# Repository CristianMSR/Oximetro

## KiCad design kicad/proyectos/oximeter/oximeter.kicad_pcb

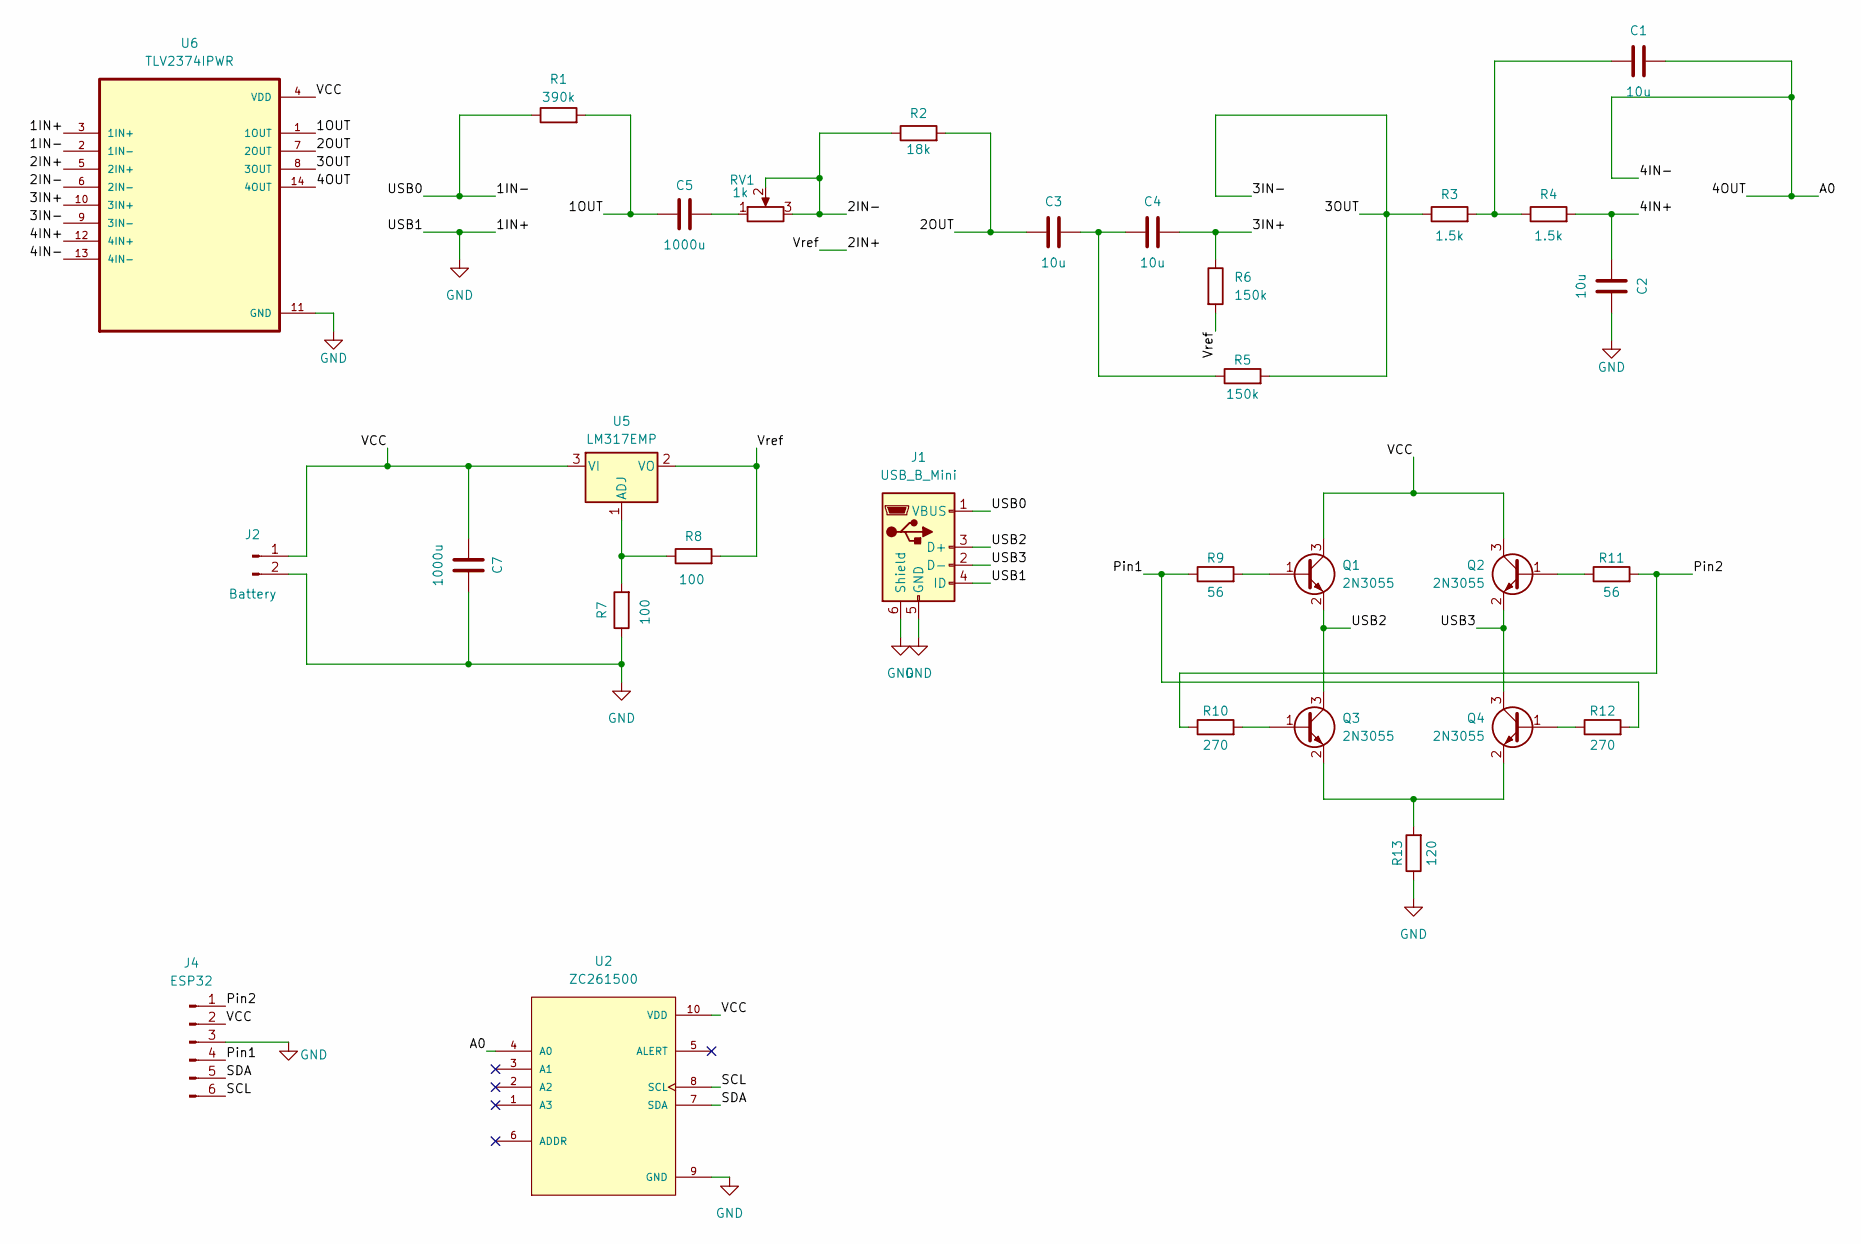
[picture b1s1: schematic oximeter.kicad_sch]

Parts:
C1, C2, C3, C4: 10u; CP_Elec_4x3
C5, C7: 1000u; CP_Radial_D8.0mm_P3.80mm
J1: USB_B_Mini; miniUSB-B-20
J2: Battery; PinHeader_1x02_P2.00mm_Vertical
J4: ESP32; PinHeader_1x06_P2.54mm_Vertical
Q1, Q2, Q3, Q4: 2N3055; BJT-NPN-SMD
R1: 390k; R_1206_3216Metric_Pad1.30x1.75mm_HandSolder
R2: 18k; R_1206_3216Metric_Pad1.30x1.75mm_HandSolder
R3, R4: 1.5k; R_1206_3216Metric_Pad1.30x1.75mm_HandSolder
R5, R6: 150k; R_1206_3216Metric_Pad1.30x1.75mm_HandSolder
R7, R8: 100; R_1206_3216Metric_Pad1.30x1.75mm_HandSolder
R9, R11: 56; R_1206_3216Metric_Pad1.30x1.75mm_HandSolder
R10, R12: 270; R_1206_3216Metric_Pad1.30x1.75mm_HandSolder
R13: 120; R_1206_3216Metric_Pad1.30x1.75mm_HandSolder
RV1: 1k; TRIM_3296W-1-103
U2: ZC261500; MODULE_ZC261500; PARTREV NA
U5: LM317EMP; SOT-223-3_TabPin2
U6: TLV2374IPWR; opamp-TLV2374IPWR

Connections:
/1IN-: J1.1 (VBUS), R1.1, U6.2 (1IN-)
/1OUT: C5.1, R1.2, U6.1 (1OUT)
/2IN+: R6.2, R8.2, U5.2 (VO), U6.5 (2IN+)
/2IN-: R2.1, RV1.2, RV1.3, U6.6 (2IN-)
/2OUT: C3.1, R2.2, U6.7 (2OUT)
/3IN+: C4.2, R6.1, U6.10 (3IN+)
/3IN-: R3.1, R5.2, U6.8 (3OUT), U6.9 (3IN-)
/4IN+: C2.1, R4.2, U6.12 (4IN+)
/4IN-: C1.2, U2.4 (A0), U6.13 (4IN-), U6.14 (4OUT)
/Pin1: J4.4, R9.1, R12.2
/Pin2: J4.1, R10.1, R11.2
/SCL: J4.6, U2.8 (SCL)
/SDA: J4.5, U2.7 (SDA)
/USB2: J1.3 (D+), Q1.2 (E), Q3.3 (C)
/USB3: J1.2 (D-), Q2.2 (E), Q4.3 (C)
/VCC: C7.1, J2.1, J4.2, Q1.3 (C), Q2.3 (C), U2.10 (VDD), U5.3 (VI), U6.4 (VDD)
GND: C2.2, C7.2, J1.4 (ID), J1.5 (GND), J1.6 (Shield), J2.2, J4.3, R7.1, R13.1, U2.9 (GND), U6.3 (1IN+), U6.11 (GND)
unnamed: C1.1, R3.2, R4.1
unnamed: C3.2, C4.1, R5.1
unnamed: C5.2, RV1.1
unnamed: Q1.1 (B), R9.2
unnamed: Q2.1 (B), R11.1
unnamed: Q3.1 (B), R10.2
unnamed: Q3.2 (E), Q4.2 (E), R13.2
unnamed: Q4.1 (B), R12.1
unnamed: R7.2, R8.1, U5.1 (ADJ)

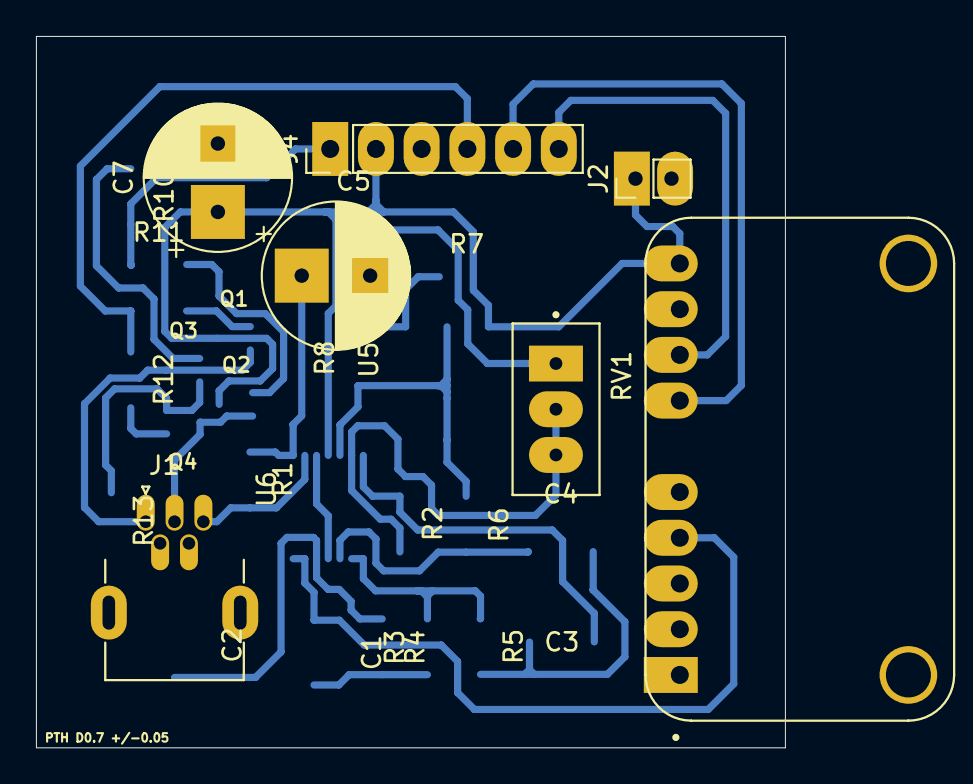
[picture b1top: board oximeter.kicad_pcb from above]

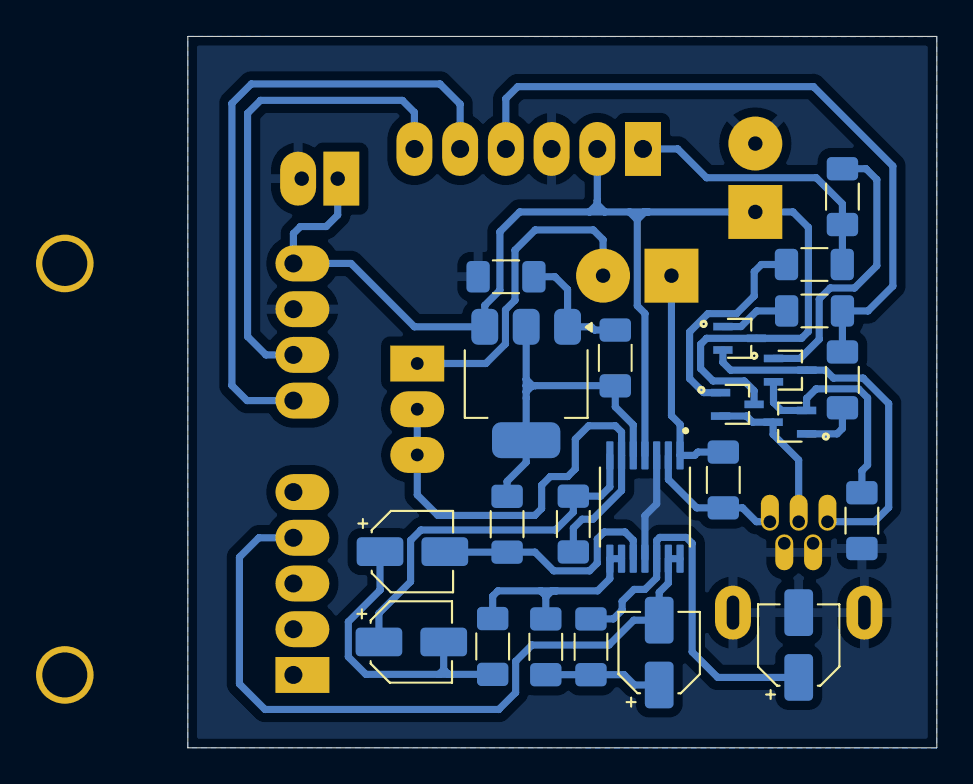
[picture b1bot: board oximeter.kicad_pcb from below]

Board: 2 copper layers, 41.6 x 39.5 mm, 30 parts (23 on the bottom side), 26 nets.

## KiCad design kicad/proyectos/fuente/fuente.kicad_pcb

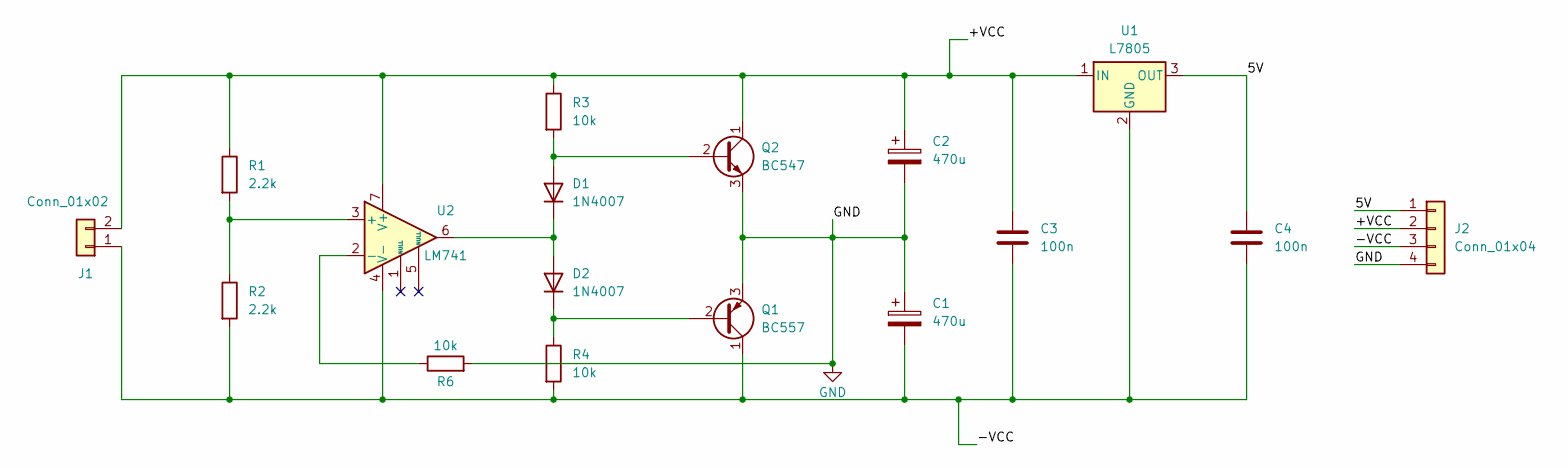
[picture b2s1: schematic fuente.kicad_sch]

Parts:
C1, C2: 470u; CP_Radial_D10.0mm_P5.00mm
C3, C4: 100n; C_Disc_D6.0mm_W2.5mm_P5.00mm
D1, D2: 1N4007; D_DO-41_SOD81_P10.16mm_Horizontal
J1: Conn_01x02; Molex_KK-254_AE-6410-02A_1x02_P2.54mm_Vertical
J2: Conn_01x04; Molex_KK-254_AE-6410-04A_1x04_P2.54mm_Vertical
Q1: BC557; TO-92_Inline
Q2: BC547; TO-92_Inline
R1, R2: 2.2k; R_Axial_DIN0207_L6.3mm_D2.5mm_P10.16mm_Horizontal
R3, R4, R6: 10k; R_Axial_DIN0207_L6.3mm_D2.5mm_P10.16mm_Horizontal
U1: L7805; L7805ACD2T
U2: LM741

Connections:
/5V: C4.1, J2.1, U1.3 (OUT)
/+VCC: C2.1, C3.1, J1.2, J2.2, Q2.1 (C), R1.1, R3.1, U1.1 (IN), U2.7 (V+)
/-VCC: C1.2, C3.2, C4.2, J1.1, J2.3, Q1.1 (C), R2.2, R4.2, U1.2 (GND), U2.4 (V-)
GND: C1.1, C2.2, J2.4, Q1.3 (E), Q2.3 (E), R6.2
unnamed: D1.2 (A), Q2.2 (B), R3.2
unnamed: D1.1 (K), D2.2 (A), U2.6
unnamed: D2.1 (K), Q1.2 (B), R4.1
unnamed: R1.2, R2.1, U2.3 (+)
unnamed: R6.1, U2.2 (-)

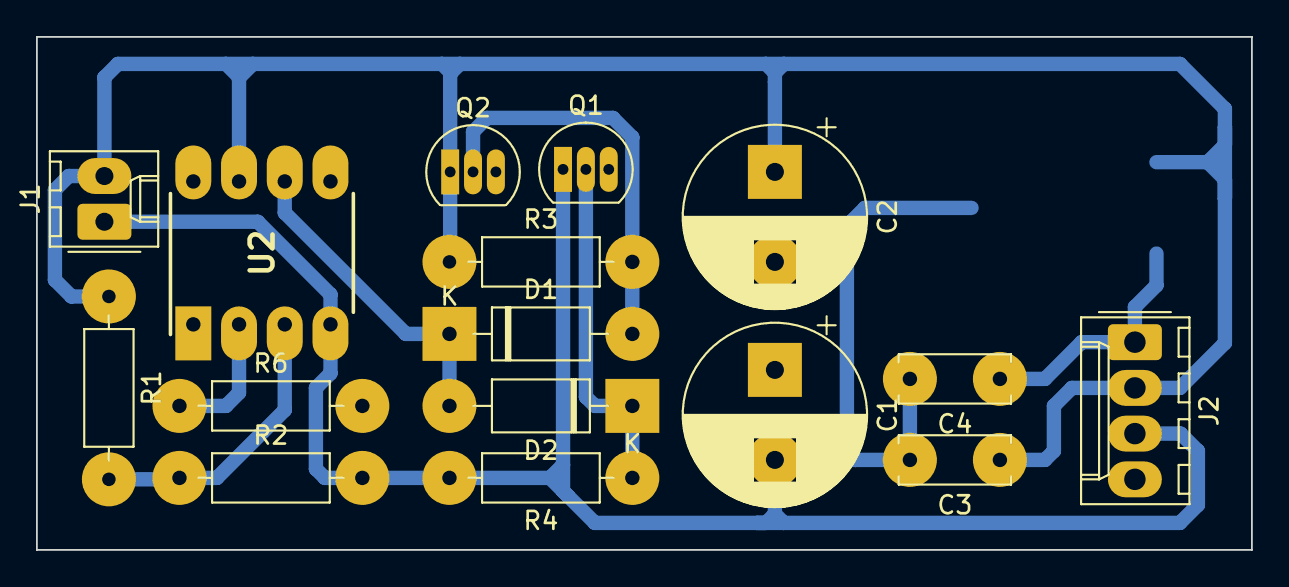
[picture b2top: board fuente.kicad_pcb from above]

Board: 2 copper layers, 67.5 x 28.5 mm, 17 parts (1 on the bottom side), 9 nets.

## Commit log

2024-10-25 Subo el proyecto completo, después ordenamos
2024-10-31 Add kicad files
2024-10-31 Change folder name in order to follow the same style
2024-11-26 Add a new paper
2024-11-26 Add some things
2024-11-28 Add Ganong theory
2024-12-03 Add paper about the project
